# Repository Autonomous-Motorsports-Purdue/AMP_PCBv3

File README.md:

# AMP_PCBv3

Files relating to version 3 of the PCB for AMP kart

## Importing project into CubeIDE

CubeIDE files are not saved to this repository.  After first clone, you will need to import the AMP_PCBv3 project into the CubeIDE workspace.

When first opening CubeIDE, open the "firmware" folder as your workspace location (do not use the "firmware/AMP_PCBv3" folder).

Once CubeIDE loads, select the "Import project" button.

Now, select the "AMP_PCBv3" folder location for the import source.

If done correctly, CubeIDE should successfully import the AMP_PCBv3 project and it should appear in the workspace.

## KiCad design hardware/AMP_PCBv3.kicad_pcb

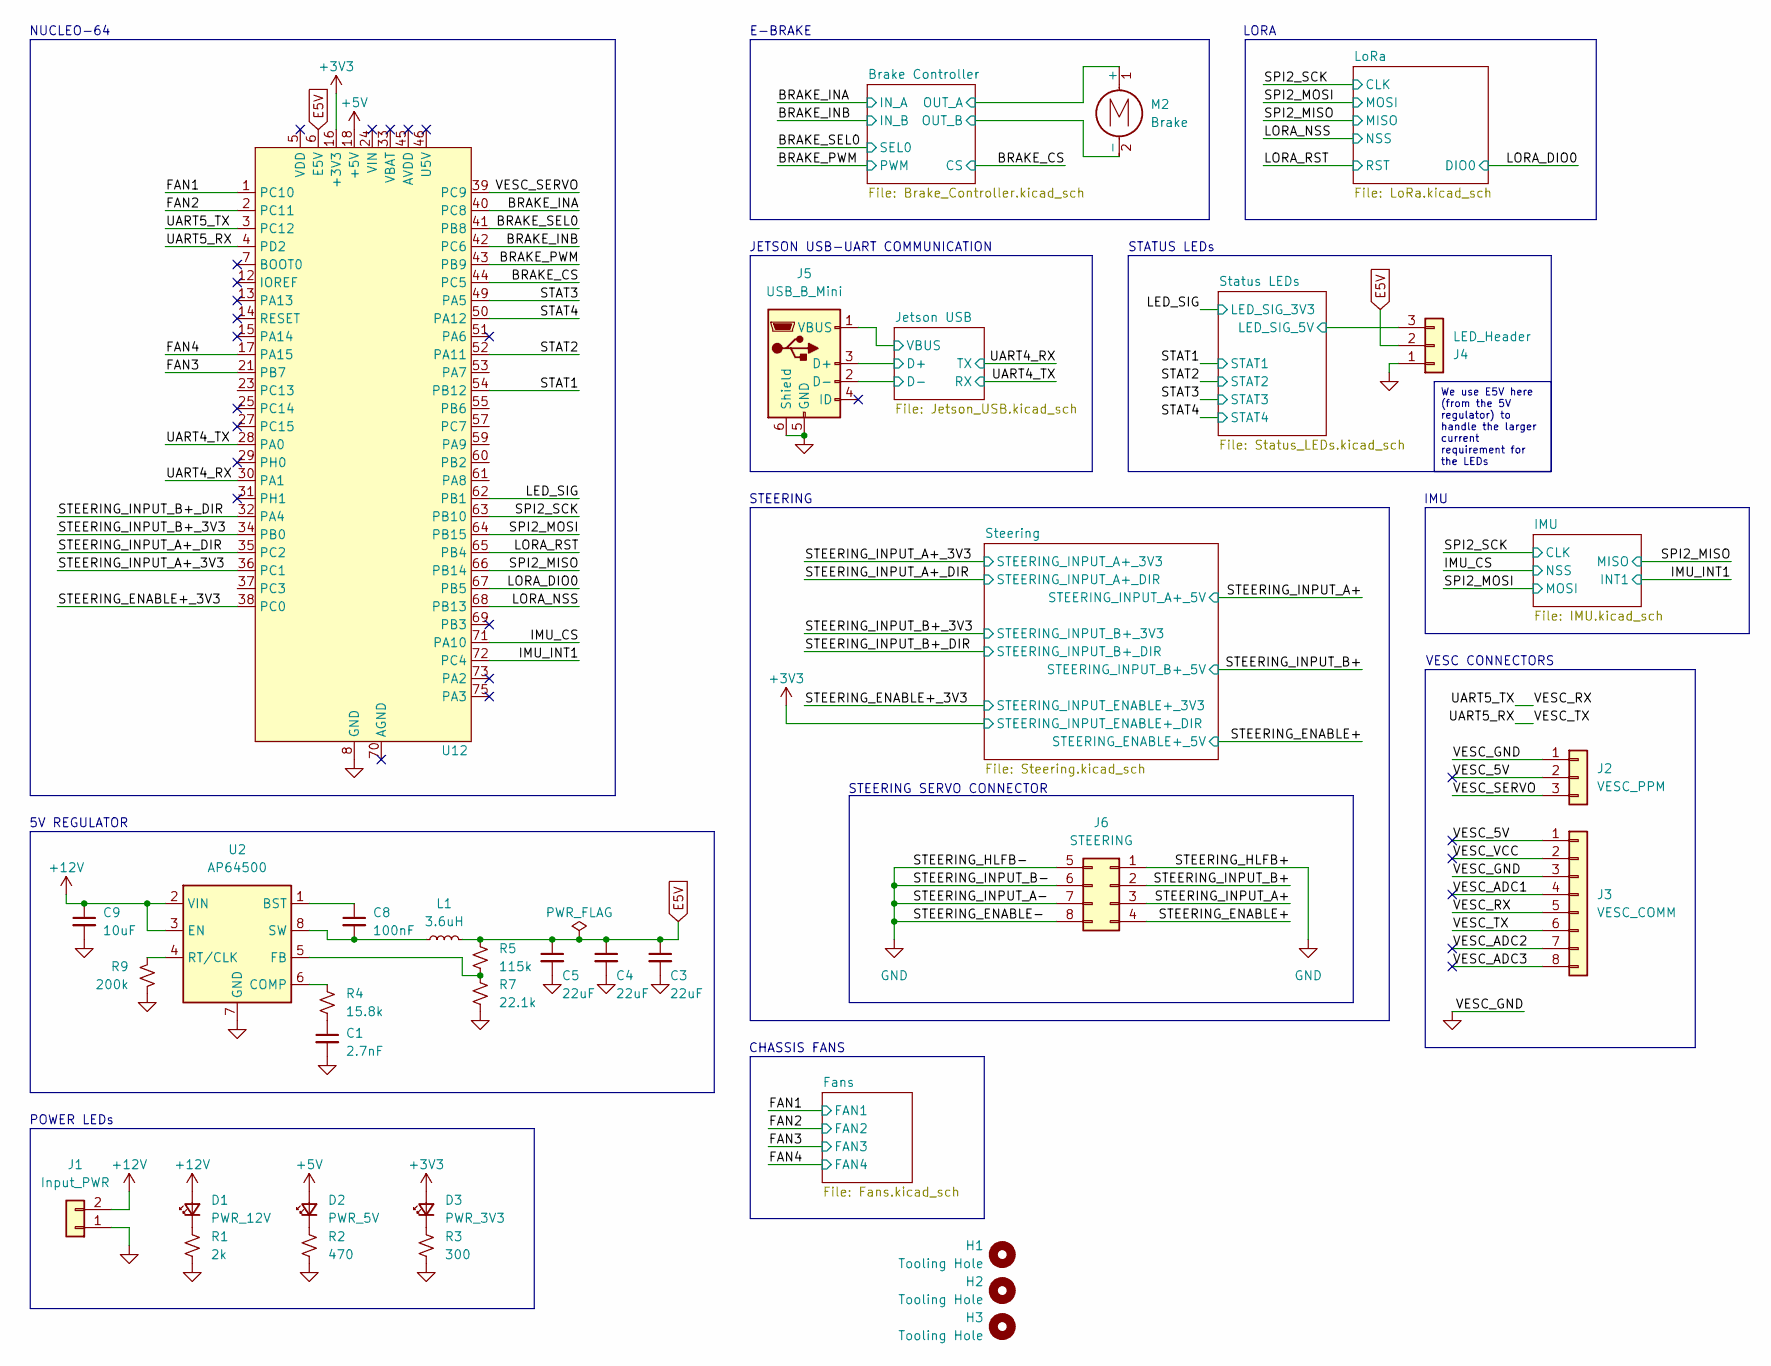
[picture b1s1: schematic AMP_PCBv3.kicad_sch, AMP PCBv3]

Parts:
C1: 2.7nF; C_0805_2012Metric_Pad1.18x1.45mm_HandSolder; MPN CL21B272KBANNNC
C3, C4, C5: 22uF; C_0805_2012Metric_Pad1.18x1.45mm_HandSolder; JLC C45783
C8: 100nF; C_0805_2012Metric_Pad1.18x1.45mm_HandSolder; JLC C49678
C9: 10uF; C_0805_2012Metric_Pad1.18x1.45mm_HandSolder; JLC C15850
D1: PWR_12V; LED_0805_2012Metric_Pad1.15x1.40mm_HandSolder; JLC C2297
D2: PWR_5V; LED_0805_2012Metric_Pad1.15x1.40mm_HandSolder; JLC C2297
D3: PWR_3V3; LED_0805_2012Metric_Pad1.15x1.40mm_HandSolder; JLC C2297
H1, H2, H3: Tooling Hole; JLCPCB_Tooling_Hole
J1: Input_PWR; Molex_Mini-Fit_Jr_5566-02A_2x01_P4.20mm_Vertical; MPN 0039281023
J2: VESC_PPM; JST_PH_B3B-PH-K_1x03_P2.00mm_Vertical; MPN B3B-PH-K-S
J3: VESC_COMM; JST_PH_B8B-PH-K_1x08_P2.00mm_Vertical; MPN B8B-PH-K-S
J4: LED_Header; Molex_KK-254_AE-6410-03A_1x03_P2.54mm_Vertical; MPN 0022272031
J5: USB_B_Mini; USB_Mini-B_Adam_Tech_MUSB-B5-S-VT-02_Vertical_CircularHoles; MPN MUSB-B5-S-VT-02
J6: STEERING; Molex_Mini-Fit_Jr_5566-08A_2x04_P4.20mm_Vertical; MPN 0039281083
L1: 3.6uH; L_Bourns-SRN8040_8x8.15mm; MPN SRN8040-3R6Y
M2: Brake; Molex_Mini-Fit_Jr_5566-02A_2x01_P4.20mm_Vertical; MPN 0039281023
R1: 2k; R_0805_2012Metric_Pad1.20x1.40mm_HandSolder; JLC C17604
R2: 470; R_0805_2012Metric_Pad1.20x1.40mm_HandSolder; JLC C17710
R3: 300; R_0805_2012Metric_Pad1.20x1.40mm_HandSolder; JLC C17617
R4: 15.8k; R_0805_2012Metric_Pad1.20x1.40mm_HandSolder; MPN RK73H2ATTD1582F
R5: 115k; R_0805_2012Metric_Pad1.20x1.40mm_HandSolder; MPN RC0805FR-07115KL
R7: 22.1k; R_0805_2012Metric_Pad1.20x1.40mm_HandSolder; MPN RMCF0805FT22K1
R9: 200k; R_0805_2012Metric_Pad1.20x1.40mm_HandSolder; JLC C17539
U2: AP64500; Diodes_SO-8EP; JLC C2070920
U12: NUCLEO64

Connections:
+5V: D2.2 (A), U12.18 (+5V); also elsewhere on the board
+12V: C9.1, D1.2 (A), J1.2, U2.2 (VIN), U2.3 (EN); also elsewhere on the board
/BRAKE_CS: U12.44 (PC5); also elsewhere on the board
/BRAKE_INA: U12.40 (PC8); also elsewhere on the board
/BRAKE_INB: U12.42 (PC6); also elsewhere on the board
/BRAKE_PWM: U12.43 (PB9); also elsewhere on the board
/BRAKE_SEL0: U12.41 (PB8); also elsewhere on the board
/Brake Controller/OUT_A: M2.1 (+); also elsewhere on the board
/Brake Controller/OUT_B: M2.2 (-); also elsewhere on the board
/FAN1: U12.1 (PC10); also elsewhere on the board
/FAN2: U12.2 (PC11); also elsewhere on the board
/FAN3: U12.21 (PB7); also elsewhere on the board
/FAN4: U12.17 (PA15); also elsewhere on the board
/IMU_CS: U12.71 (PA10); also elsewhere on the board
/IMU_INT1: U12.72 (PC4); also elsewhere on the board
/Jetson USB/D+: J5.3 (D+); also elsewhere on the board
/Jetson USB/D-: J5.2 (D-); also elsewhere on the board
/Jetson USB/VBUS: J5.1 (VBUS); also elsewhere on the board
/LED_SIG: U12.62 (PB1); also elsewhere on the board
/LORA_DIO0: U12.67 (PB5); also elsewhere on the board
/LORA_NSS: U12.68 (PB13); also elsewhere on the board
/LORA_RST: U12.65 (PB4); also elsewhere on the board
/SPI2_MISO: U12.66 (PB14); also elsewhere on the board
/SPI2_MOSI: U12.64 (PB15); also elsewhere on the board
/SPI2_SCK: U12.63 (PB10); also elsewhere on the board
/STAT1: U12.54 (PB12); also elsewhere on the board
/STAT2: U12.52 (PA11); also elsewhere on the board
/STAT3: U12.49 (PA5); also elsewhere on the board
/STAT4: U12.50 (PA12); also elsewhere on the board
/STEERING_ENABLE+: J6.4; also elsewhere on the board
/STEERING_ENABLE+_3V3: U12.38 (PC0); also elsewhere on the board
/STEERING_INPUT_A+: J6.3; also elsewhere on the board
/STEERING_INPUT_A+_3V3: U12.36 (PC1); also elsewhere on the board
/STEERING_INPUT_A+_DIR: U12.35 (PC2); also elsewhere on the board
/STEERING_INPUT_B+: J6.2; also elsewhere on the board
/STEERING_INPUT_B+_3V3: U12.34 (PB0); also elsewhere on the board
/STEERING_INPUT_B+_DIR: U12.32 (PA4); also elsewhere on the board
/Status LEDs/LED_SIG_5V: J4.3; also elsewhere on the board
/UART4_RX: U12.30 (PA1); also elsewhere on the board
/UART4_TX: U12.28 (PA0); also elsewhere on the board
/UART5_RX: J3.6, U12.4 (PD2)
/UART5_TX: J3.5, U12.3 (PC12)
/VESC_5V: J2.2, J3.1
/VESC_ADC1: J3.4
/VESC_ADC2: J3.7
/VESC_ADC3: J3.8
/VESC_SERVO: J2.3, U12.39 (PC9)
/VESC_VCC: J3.2
E5V: C3.1, C4.1, C5.1, J4.2, L1.2, R5.1, U12.6 (E5V); also elsewhere on the board
GND: C1.2, C3.2, C4.2, C5.2, C9.2, J1.1, J2.1, J3.3, J4.1, J5.5 (GND), J5.6 (Shield), J6.1, J6.5, J6.6, J6.7, J6.8, R1.2, R2.2, R3.2, R7.2, R9.1, U2.7 (GND), U2.9 (GND), U12.8 (GND), U12.19 (GND), U12.20 (GND), U12.22 (GND), U12.47 (GND), U12.58 (GND); also elsewhere on the board
unnamed: C1.1, R4.1
unnamed: D1.1 (K), R1.1
unnamed: D2.1 (K), R2.1
unnamed: D3.1 (K), R3.1
unnamed: C8.1, U2.1 (BST)
unnamed: R4.2, U2.6 (COMP)
unnamed: R5.2, R7.1, U2.5 (FB)
unnamed: R9.2, U2.4 (RT/CLK)
unnamed: C8.2, L1.1, U2.8 (SW)

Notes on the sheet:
We use E5V here (from the 5V regulator) to handle the larger current requirement for the LEDs
NUCLEO-64
LORA
STEERING SERVO CONNECTOR
E-BRAKE
5V REGULATOR
STEERING
STATUS LEDs
VESC CONNECTORS
POWER LEDs
IMU
CHASSIS FANS
JETSON USB-UART COMMUNICATION

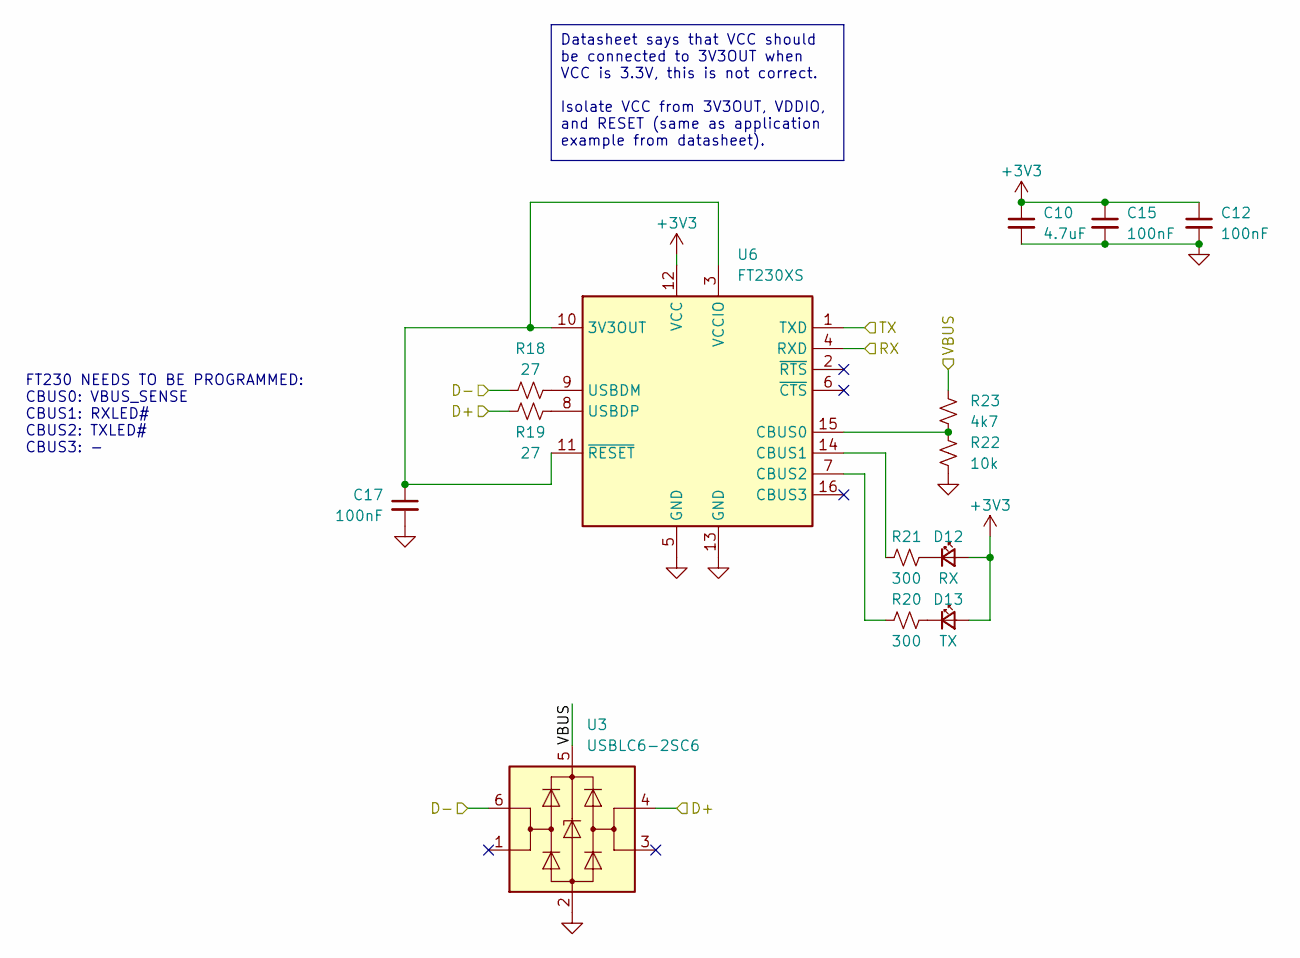
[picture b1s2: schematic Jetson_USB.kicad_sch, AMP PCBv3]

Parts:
C10: 4.7uF; C_0805_2012Metric_Pad1.18x1.45mm_HandSolder; JLC C1779
C12, C15, C17: 100nF; C_0805_2012Metric_Pad1.18x1.45mm_HandSolder; JLC C49678
D12: RX; LED_0805_2012Metric_Pad1.15x1.40mm_HandSolder; JLC C84256
D13: TX; LED_0805_2012Metric_Pad1.15x1.40mm_HandSolder; JLC C84256
R18, R19: 27; R_0805_2012Metric_Pad1.20x1.40mm_HandSolder; MPN RC0805JR-0727RL
R20, R21: 300; R_0805_2012Metric_Pad1.20x1.40mm_HandSolder; JLC C17617
R22: 10k; R_0805_2012Metric_Pad1.20x1.40mm_HandSolder; JLC C17414
R23: 4k7; R_0805_2012Metric_Pad1.20x1.40mm_HandSolder; JLC C17673
U3: USBLC6-2SC6; SOT-23-6; JLC C2827654
U6: FT230XS; SSOP-16_3.9x4.9mm_P0.635mm; JLC C69082

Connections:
/Jetson USB/D+: R19.1, U3.4 (I/O2); also elsewhere on the board
/Jetson USB/D-: R18.1, U3.6 (I/O1); also elsewhere on the board
/Jetson USB/VBUS: R23.1, U3.5 (VBUS); also elsewhere on the board
/UART4_RX: U6.1 (TXD); also elsewhere on the board
/UART4_TX: U6.4 (RXD); also elsewhere on the board
GND: C10.2, C12.2, C15.2, C17.2, R22.2, U3.2 (GND), U6.5 (GND), U6.13 (GND); also elsewhere on the board
unnamed: D12.1 (K), R21.2
unnamed: D13.1 (K), R20.2
unnamed: R22.1, R23.2, U6.15 (CBUS0)
unnamed: R21.1, U6.14 (CBUS1)
unnamed: R20.1, U6.7 (CBUS2)
unnamed: R18.2, U6.9 (USBDM)
unnamed: R19.2, U6.8 (USBDP)

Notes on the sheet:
Datasheet says that VCC should be connected to 3V3OUT when VCC is 3.3V, this is not correct. Isolate VCC from 3V3OUT, VDDIO, and RESET (same as application example from datasheet).
FT230 NEEDS TO BE PROGRAMMED: CBUS0: VBUS_SENSE CBUS1: RXLED# CBUS2: TXLED# CBUS3: -

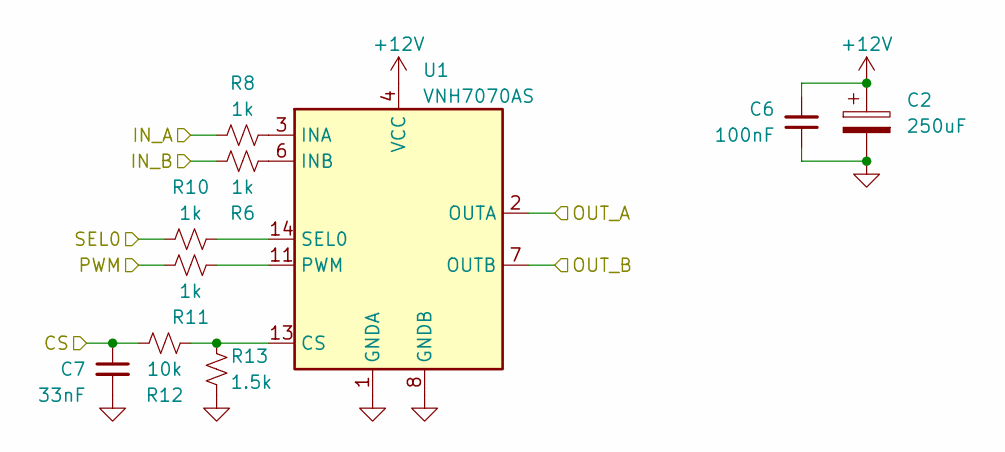
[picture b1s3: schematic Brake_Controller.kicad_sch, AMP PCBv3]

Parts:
C2: 250uF; CP_Radial_D8.0mm_P3.50mm; MPN A750KS227M1EAAE015
C6: 100nF; C_0805_2012Metric_Pad1.18x1.45mm_HandSolder; JLC C49678
C7: 33nF; C_0805_2012Metric_Pad1.18x1.45mm_HandSolder; JLC C1739
R6, R8, R10, R11: 1k; R_0805_2012Metric_Pad1.20x1.40mm_HandSolder; JLC C17513
R12: 10k; R_0805_2012Metric_Pad1.20x1.40mm_HandSolder; JLC C17414
R13: 1.5k; R_0805_2012Metric_Pad1.20x1.40mm_HandSolder; JLC C4310
U1: VNH7070AS; SOP-16_3.9x9.9mm_P1.27mm; JLC C2150622

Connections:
+12V: C2.1, C6.2, U1.4 (VCC), U1.5 (VCC), U1.12 (VCC); also elsewhere on the board
/BRAKE_CS: C7.1, R12.1; also elsewhere on the board
/BRAKE_INA: R8.1; also elsewhere on the board
/BRAKE_INB: R6.2; also elsewhere on the board
/BRAKE_PWM: R11.2; also elsewhere on the board
/BRAKE_SEL0: R10.1; also elsewhere on the board
/Brake Controller/OUT_A: U1.2 (OUTA), U1.15 (OUTA); also elsewhere on the board
/Brake Controller/OUT_B: U1.7 (OUTB), U1.10 (OUTB); also elsewhere on the board
GND: C2.2, C6.1, C7.2, R13.2, U1.1 (GNDA), U1.8 (GNDB), U1.9 (GNDB), U1.16 (GNDA); also elsewhere on the board
unnamed: R12.2, R13.1, U1.13 (CS)
unnamed: R8.2, U1.3 (INA)
unnamed: R6.1, U1.6 (INB)
unnamed: R11.1, U1.11 (PWM)
unnamed: R10.2, U1.14 (SEL0)

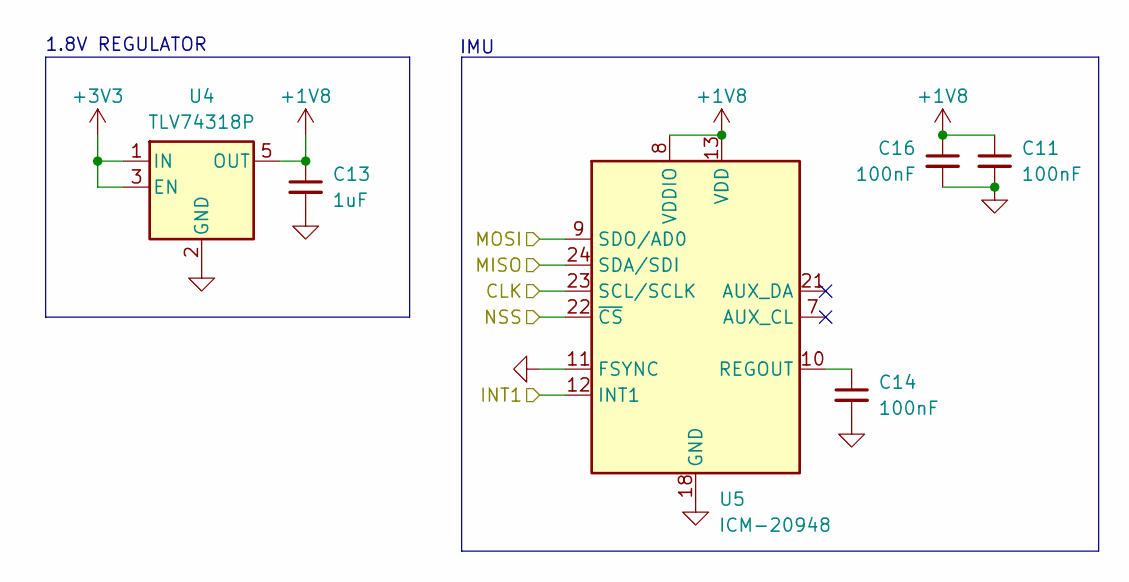
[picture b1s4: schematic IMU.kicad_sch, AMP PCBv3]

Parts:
C11, C14, C16: 100nF; C_0805_2012Metric_Pad1.18x1.45mm_HandSolder; JLC C49678
C13: 1uF; C_0805_2012Metric_Pad1.18x1.45mm_HandSolder; JLC C28323
U4: TLV74318P; SOT-23-5_HandSoldering; JLC C485152
U5: ICM-20948; InvenSense_QFN-24_3x3mm_P0.4mm; JLC C726001

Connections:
+1V8: C11.1, C13.1, C16.1, U4.5 (OUT), U5.8 (VDDIO), U5.13 (VDD)
/IMU_CS: U5.22 (~CS); also elsewhere on the board
/IMU_INT1: U5.12 (INT1); also elsewhere on the board
/SPI2_MISO: U5.24 (SDA/SDI); also elsewhere on the board
/SPI2_MOSI: U5.9 (SDO/AD0); also elsewhere on the board
/SPI2_SCK: U5.23 (SCL/SCLK); also elsewhere on the board
GND: C11.2, C13.2, C14.2, C16.2, U4.2 (GND), U5.11 (FSYNC), U5.18 (GND), U5.20 (GND); also elsewhere on the board
unnamed: C14.1, U5.10 (REGOUT)

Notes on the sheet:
1.8V REGULATOR
IMU

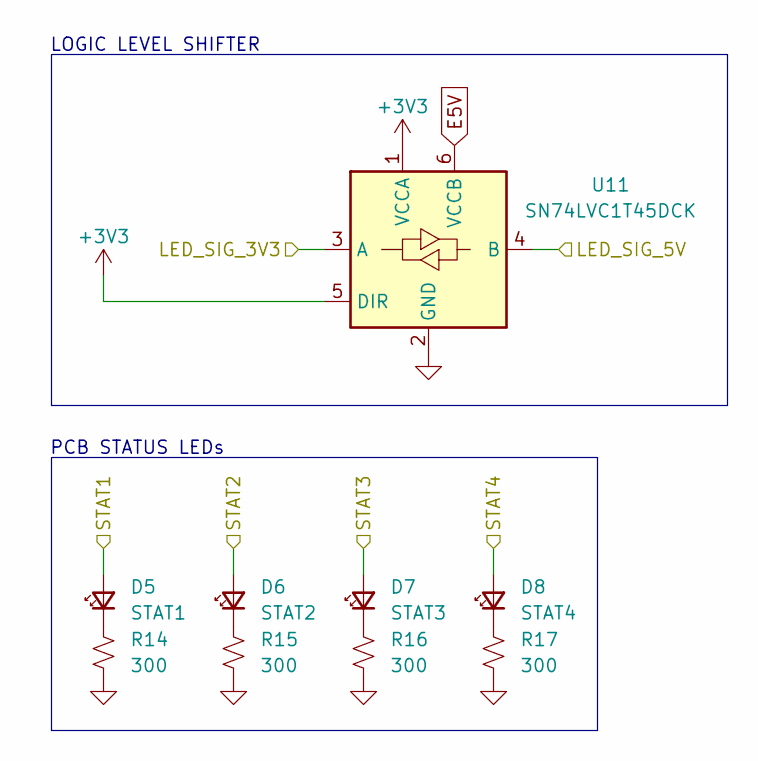
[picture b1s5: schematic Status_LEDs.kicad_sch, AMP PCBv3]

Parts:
D5: STAT1; LED_0805_2012Metric_Pad1.15x1.40mm_HandSolder; JLC C2296
D6: STAT2; LED_0805_2012Metric_Pad1.15x1.40mm_HandSolder; JLC C2296
D7: STAT3; LED_0805_2012Metric_Pad1.15x1.40mm_HandSolder; JLC C2296
D8: STAT4; LED_0805_2012Metric_Pad1.15x1.40mm_HandSolder; JLC C84256
R14, R15, R16, R17: 300; R_0805_2012Metric_Pad1.20x1.40mm_HandSolder; JLC C17617
U11: SN74LVC1T45DCK; SOT-363_SC-70-6; JLC C9382

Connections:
/LED_SIG: U11.3 (A); also elsewhere on the board
/STAT1: D5.2 (A); also elsewhere on the board
/STAT2: D6.2 (A); also elsewhere on the board
/STAT3: D7.2 (A); also elsewhere on the board
/STAT4: D8.2 (A); also elsewhere on the board
/Status LEDs/LED_SIG_5V: U11.4 (B); also elsewhere on the board
E5V: U11.6 (VCCB); also elsewhere on the board
GND: R14.2, R15.2, R16.2, R17.2, U11.2 (GND); also elsewhere on the board
unnamed: D5.1 (K), R14.1
unnamed: D6.1 (K), R15.1
unnamed: D7.1 (K), R16.1
unnamed: D8.1 (K), R17.1

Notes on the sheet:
LOGIC LEVEL SHIFTER
PCB STATUS LEDs

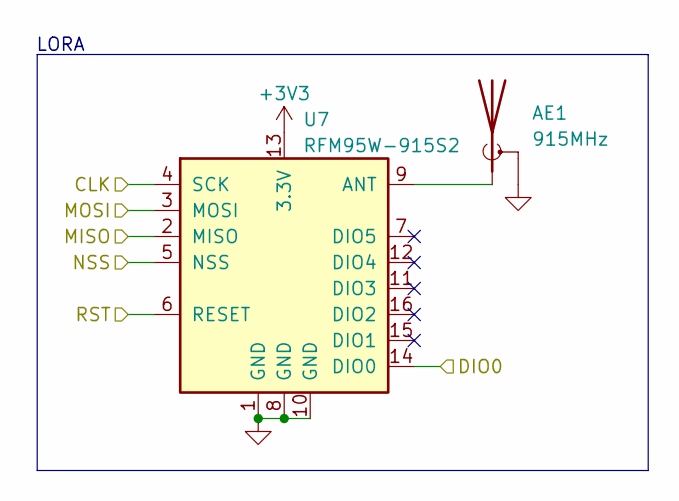
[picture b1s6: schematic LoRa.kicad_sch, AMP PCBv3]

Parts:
AE1: 915MHz; SMA_Amphenol_132291_Vertical; MPN CONSMA001-C-G
U7: RFM95W-915S2; HOPERF_RFM9XW_SMD; MPN RFM95W-915S2

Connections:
/LORA_DIO0: U7.14 (DIO0); also elsewhere on the board
/LORA_NSS: U7.5 (NSS); also elsewhere on the board
/LORA_RST: U7.6 (RESET); also elsewhere on the board
/SPI2_MISO: U7.2 (MISO); also elsewhere on the board
/SPI2_MOSI: U7.3 (MOSI); also elsewhere on the board
/SPI2_SCK: U7.4 (SCK); also elsewhere on the board
GND: AE1.2 (Shield), U7.1 (GND), U7.8 (GND), U7.10 (GND); also elsewhere on the board
unnamed: AE1.1 (A), U7.9 (ANT)

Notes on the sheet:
LORA

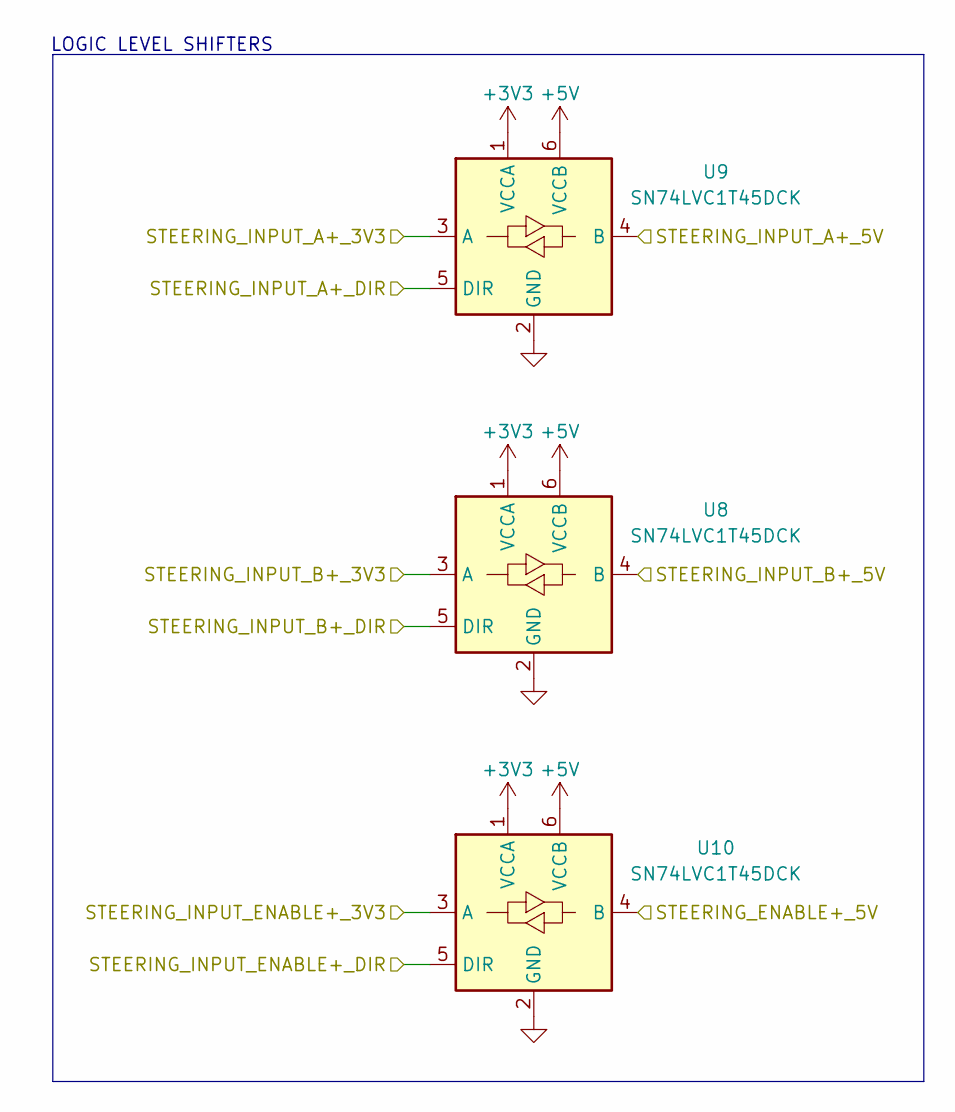
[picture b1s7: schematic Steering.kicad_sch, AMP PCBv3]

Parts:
U8, U9, U10: SN74LVC1T45DCK; SOT-363_SC-70-6; JLC C9382

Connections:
+5V: U8.6 (VCCB), U9.6 (VCCB), U10.6 (VCCB); also elsewhere on the board
/STEERING_ENABLE+: U10.4 (B); also elsewhere on the board
/STEERING_ENABLE+_3V3: U10.3 (A); also elsewhere on the board
/STEERING_INPUT_A+: U9.4 (B); also elsewhere on the board
/STEERING_INPUT_A+_3V3: U9.3 (A); also elsewhere on the board
/STEERING_INPUT_A+_DIR: U9.5 (DIR); also elsewhere on the board
/STEERING_INPUT_B+: U8.4 (B); also elsewhere on the board
/STEERING_INPUT_B+_3V3: U8.3 (A); also elsewhere on the board
/STEERING_INPUT_B+_DIR: U8.5 (DIR); also elsewhere on the board
GND: U8.2 (GND), U9.2 (GND), U10.2 (GND); also elsewhere on the board

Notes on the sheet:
LOGIC LEVEL SHIFTERS

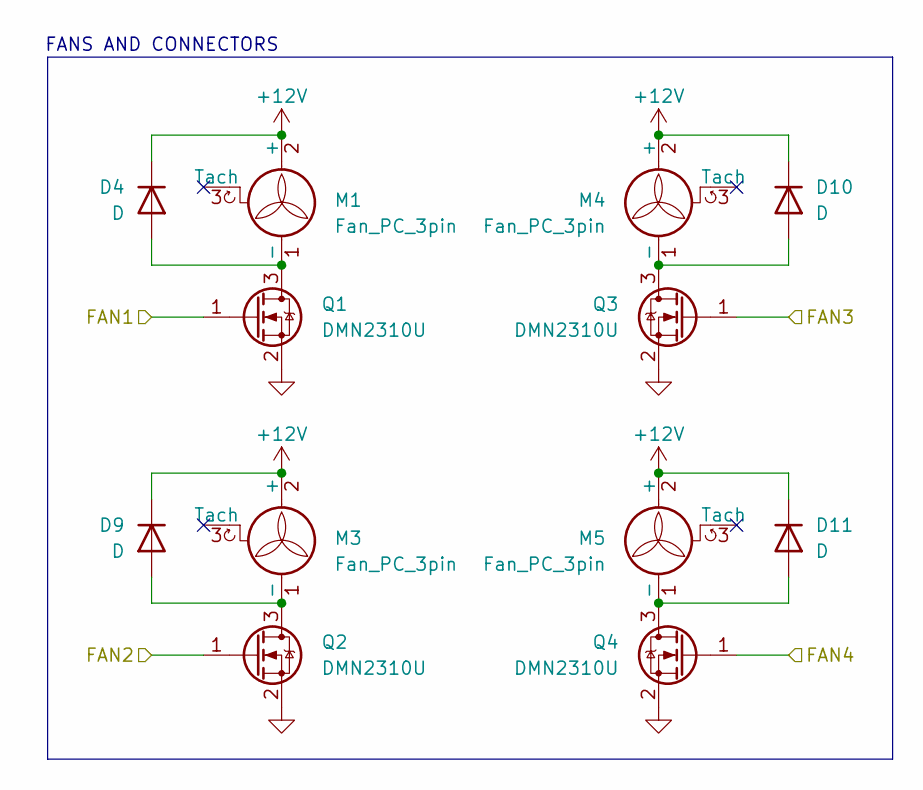
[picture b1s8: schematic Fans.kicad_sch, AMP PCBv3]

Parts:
D4, D9, D10, D11: D; D_SOD-323F; JLC C2128
M1, M3, M4, M5: Fan_PC_3pin; Molex_KK-254_AE-6410-03A_1x03_P2.54mm_Vertical; MPN 0022272031
Q1, Q2, Q3, Q4: DMN2310U; SOT-23; JLC C20917

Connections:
+12V: D4.1 (K), D9.1 (K), D10.1 (K), D11.1 (K), M1.2 (+), M3.2 (+), M4.2 (+), M5.2 (+); also elsewhere on the board
/FAN1: Q1.1 (G); also elsewhere on the board
/FAN2: Q2.1 (G); also elsewhere on the board
/FAN3: Q3.1 (G); also elsewhere on the board
/FAN4: Q4.1 (G); also elsewhere on the board
GND: Q1.2 (S), Q2.2 (S), Q3.2 (S), Q4.2 (S); also elsewhere on the board
unnamed: D4.2 (A), M1.1 (-), Q1.3 (D)
unnamed: D9.2 (A), M3.1 (-), Q2.3 (D)
unnamed: D10.2 (A), M4.1 (-), Q3.3 (D)
unnamed: D11.2 (A), M5.1 (-), Q4.3 (D)

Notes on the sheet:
FANS AND CONNECTORS

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
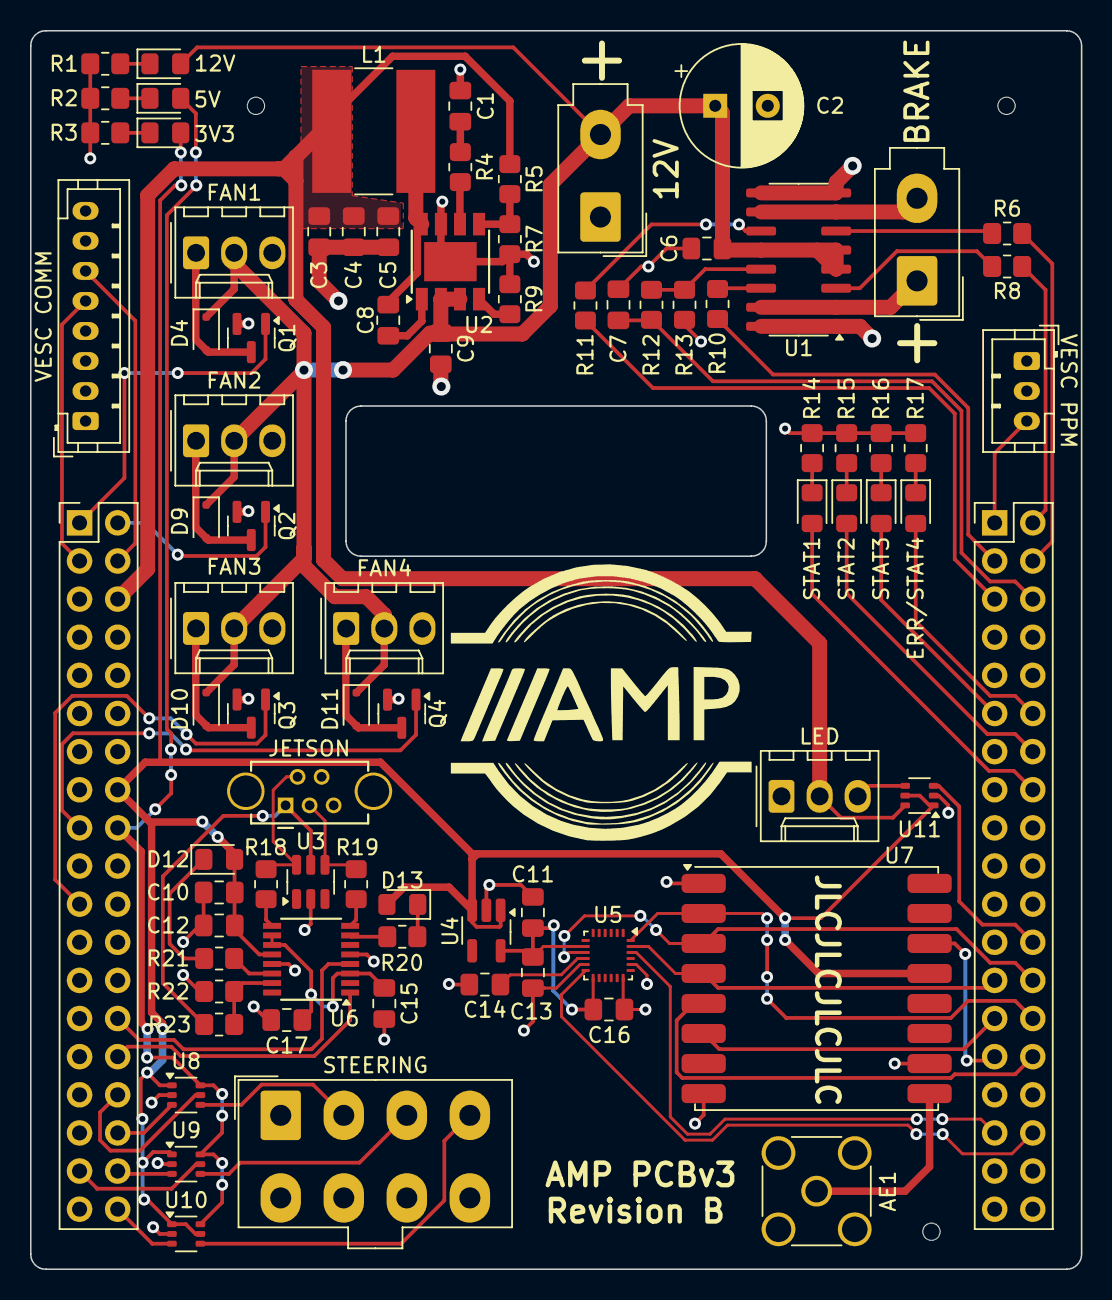
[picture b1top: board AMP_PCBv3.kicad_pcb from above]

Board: 2 copper layers, 70.0 x 82.5 mm, 85 parts (0 on the bottom side), 80 nets.

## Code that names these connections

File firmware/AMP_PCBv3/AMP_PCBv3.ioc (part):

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Mcu.Name=STM32F446R(C-E)Tx
Mcu.Package=LQFP64
Mcu.UserName=STM32F446RETx
PA0-WKUP.Mode=Asynchronous
PA0-WKUP.Signal=UART4_TX
PA1.Mode=Asynchronous
PA1.Signal=UART4_RX
PA10.GPIOParameters=GPIO_Label
PA10.GPIO_Label=IMU_CS
PA10.Signal=GPIO_Output
PA11.GPIOParameters=GPIO_Label
PA11.GPIO_Label=STAT2
PA11.Signal=GPIO_Output
PA12.GPIOParameters=GPIO_Label
PA12.GPIO_Label=STAT4
PA12.Signal=GPIO_Output
PA13.GPIOParameters=GPIO_Label
PA13.GPIO_Label=TMS
PA13.Mode=Serial_Wire
PA13.Signal=SYS_JTMS-SWDIO
PA14.GPIOParameters=GPIO_Label
PA14.GPIO_Label=TCK
PA14.Mode=Serial_Wire
PA14.Signal=SYS_JTCK-SWCLK
PA15.GPIOParameters=GPIO_Label
PA15.GPIO_Label=FAN4
PA15.Signal=GPIO_Output
PA2.GPIOParameters=GPIO_Label
PA2.GPIO_Label=USART_TX
PA2.Mode=Asynchronous
PA2.Signal=USART2_TX
PA3.GPIOParameters=GPIO_Label
PA3.GPIO_Label=USART_RX
PA3.Mode=Asynchronous
PA3.Signal=USART2_RX
PA4.GPIOParameters=GPIO_Label
PA4.GPIO_Label=STR_INPUTB+_DIR
PA4.Signal=GPIO_Output
PA5.GPIOParameters=GPIO_Label
PA5.GPIO_Label=STAT3[GREEN_LED]
PA5.Signal=GPIO_Output
PB0.GPIOParameters=GPIO_Label
PB0.GPIO_Label=STR_INPUTB+
PB0.Signal=S_TIM3_CH3
PB1.Mode=PWM Generation3 CH3N
PB1.Signal=TIM1_CH3N
PB10.Mode=Full_Duplex_Master
PB10.Signal=SPI2_SCK
PB12.GPIOParameters=GPIO_Label
PB12.GPIO_Label=STAT1
PB12.Signal=GPIO_Output
PB13.GPIOParameters=GPIO_Label
PB13.GPIO_Label=LORA_NSS
PB13.Signal=GPIO_Output
PB14.Mode=Full_Duplex_Master
PB14.Signal=SPI2_MISO
PB15.Mode=Full_Duplex_Master
PB15.Signal=SPI2_MOSI
PB3.GPIOParameters=GPIO_Label
PB3.GPIO_Label=SWO
PB3.Signal=SYS_JTDO-SWO
PB4.GPIOParameters=GPIO_Label
PB4.GPIO_Label=LORA_RST
PB4.Signal=GPIO_Output
PB5.GPIOParameters=GPIO_Label
PB5.GPIO_Label=LORA_DIO0
PB5.Signal=GPXTI5
PB6.Signal=S_TIM4_CH1
PB7.GPIOParameters=GPIO_Label
PB7.GPIO_Label=FAN3
PB7.Signal=GPIO_Output
PB8.GPIOParameters=GPIO_Label
PB8.GPIO_Label=BRAKE_SEL0
PB8.Signal=GPIO_Output
PB9.GPIOParameters=GPIO_Label
PB9.GPIO_Label=BRAKE_PWM
PB9.Signal=GPIO_Output
PC0.GPIOParameters=GPIO_Label
PC0.GPIO_Label=STR_EN+
PC0.Signal=GPIO_Output
PC1.GPIOParameters=GPIO_Label
PC1.GPIO_Label=STR_INPUTA+
PC1.Signal=GPIO_Output
PC10.GPIOParameters=GPIO_Label
PC10.GPIO_Label=FAN1
PC10.Signal=GPIO_Output
PC11.GPIOParameters=GPIO_Label
PC11.GPIO_Label=FAN2
PC11.Signal=GPIO_Output
PC12.Mode=Asynchronous
PC12.Signal=UART5_TX
PC13.GPIOParameters=GPIO_Label,GPIO_ModeDefaultEXTI
PC13.GPIO_Label=B1 [BLUE BUTTON]
PC13.GPIO_ModeDefaultEXTI=GPIO_MODE_IT_FALLING
PC13.Signal=GPXTI13
PC14-OSC32_IN.Mode=LSE-External-Oscillator
PC14-OSC32_IN.Signal=RCC_OSC32_IN
PC15-OSC32_OUT.Mode=LSE-External-Oscillator
PC15-OSC32_OUT.Signal=RCC_OSC32_OUT
PC2.GPIOParameters=GPIO_Label
PC2.GPIO_Label=STR_INPUTA+_DIR
PC2.Signal=GPIO_Output
PC4.GPIOParameters=GPIO_Label
PC4.GPIO_Label=IMU_INT1
PC4.Signal=GPXTI4
PC5.GPIOParameters=GPIO_Label
PC5.GPIO_Label=BRAKE_CS
PC5.Signal=ADCx_IN15
PC6.GPIOParameters=GPIO_Label
PC6.GPIO_Label=BRAKE_INB
PC6.Signal=GPIO_Output
PC8.GPIOParameters=GPIO_Label
PC8.GPIO_Label=BRAKE_INA
PC8.Signal=GPIO_Output
PC9.GPIOParameters=GPIO_Label
PC9.GPIO_Label=VESC_PPM
PC9.Signal=S_TIM8_CH4
PD2.Mode=Asynchronous
PD2.Signal=UART5_RX
PH0-OSC_IN.Mode=HSE-External-Oscillator
PH0-OSC_IN.Signal=RCC_OSC_IN
PH1-OSC_OUT.Mode=HSE-External-Oscillator
PH1-OSC_OUT.Signal=RCC_OSC_OUT
RCC.HSE_VALUE=8000000
RCC.SYSCLKFreq_VALUE=180000000
RCC.SYSCLKSource=RCC_SYSCLKSOURCE_PLLCLK
board=NUCLEO-F446RE
boardIOC=true

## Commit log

2024-02-09 Add Nucleo headers and rough PCB shape
2024-02-10 Add power circuitry and begin routing
2024-02-10 Add USB/UART and more routing
2024-02-10 Ignore locked files
2024-02-10 Add new brake controller and inductor 3D model
2024-02-10 Add IMU schematic
2024-03-13 Add fan headers and place components
2024-03-13 Create STM32 project and map signals in IOC
2024-03-14 Update IOC with steering pins
2024-03-14 Add steering connector and route board (4 layers)
2024-04-02 Changes to be updated
2024-04-02 Resize board and begin new layout
2024-04-02 Add level shifters
2024-04-03 Place and route
2024-04-03 Add level shifter for LEDs
2024-04-03 JLC assembly parts
2024-04-03 Schematic cleanup
2024-04-03 Final touches for assembly
2024-04-14 Code generation
2024-04-14 fan functions added
2024-04-14 Added ebrake functions
2024-04-15 Update revision
2024-04-15 Fix #10
2024-04-15 Fix #6
2024-04-19 Change existing driver format and setup state machine skeleton
2024-04-19 Remove some fan driver functions
2024-04-19 Add status LED driver
2024-04-19 Move LoRa initialization to state machine
2024-04-19 Miscellaneous changes to IOC
2024-04-21 Sunday testing
2024-04-22 Add console control mode
2024-04-22 started steering PWM
2024-04-22 Add steering functions and fix duty cycle
2024-04-22 Ignore metadata folder
2024-04-22 More folders
2024-04-22 Test
2024-04-22 More testing gitignore
2024-04-22 Undo gitignore changes
2024-04-22 Fix errors from merge
2024-04-22 Fix UART bug where too long input would infinite loop
2024-04-22 Literally make the same changes I hate git
2024-04-22 Remove files
2024-04-22 Keep removed folders gone
2024-04-22 Ignore .DS_Store file
2024-04-22 Add information about how to import to CubeIDE
2024-04-22 Add clarity
2024-04-23 Rename status LED driver to debug LED driver
2024-04-23 Rename debug LED driver
2024-04-23 Fix pin assignments
2024-04-24 Include dependencies for all build targets
2024-04-24 Add throttle driver
2024-04-24 Add ability to enter negative throttle in console mode
2024-04-24 Force autonomous direction to always be forward
2024-04-29 Incorrect purple color
2024-04-29 Clean up color select code
2024-04-29 Update throttle value every tick
2024-04-29 Add easy way to go to AUTO state without remote control
2024-05-01 Extend the e-brake during init to avoid long-term damage
2024-10-19 Isolate VCC from 3V3OUT, VDDIO, and nRESET (same as application example from datasheet)
2024-10-19 Update PCB to reflect changes
2025-03-30 init lora
2025-10-26 arduino conversion
2025-11-09 testing controller
2026-02-22 updated for uart
2026-04-26 testing changes
